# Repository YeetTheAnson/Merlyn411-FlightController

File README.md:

# Merlyn411 Flight Controller

> [!TIP]
> The Merlyn411 is outdated! Check out the [Merlyn435](https://github.com/YeetTheAnson/Merlyn435-Flight-Stack/) for a more powerful and modern flight controller + ESC.

## Introduction

This is my custom AIO (No ESC) flight controller! I started this project because commercial flight controllers get very expensive very quickly as you demand for more features like integrated radio receivers. I took on the challenge of designing my own betaflight compatible flight controller and it was difficult especially since the board has only 2 layers to save as much cost as possible and it's also my first time working with RF in circuits.

This flight controller is designed for a wide range of drones from 2" to as big as you want it to, and supports battery voltage from 2s to 8s although it is recommended to use a maximum of 6s. The 25.5mm pattern should be compatible with almost all frames on the market

It also features many quality of life features like an integrated ExpressLRS (ELRS) 2.4GHz receiver, an onboard OSD which inserts telemetry directly into the FPV video feed, 16MB flash memory for flight & blackbox logging and a buzzer for identifying error codes and to locate the drone.

While the primary focus of this projet is the flight controller hardware and firmware, I have also included a guide for the full 3 inch long range / freestyle drone build that this board was designed for

-----

## Hardware Specifications

  - **MCU:** STM32F411CEU6 (100MHz, 512KB Flash)
  - **IMU:** MPU6500 (SPI)
  - **OSD:** AT7456E (SPI)
  - **Blackbox:** Winbond W25Q128 16MB Flash (SPI)
  - **Receiver:** Integrated 2.4GHz ExpressLRS (ESP8285 & SX1281)
  - **Power Supply:** 5v and 3.3v rails up to 1A (3.3v rail is limited to 250mA)
  - **Mounting:** 25.5mm x 25.5mm square mounting pattern with M3 holes
  - **Peripherals** Includes pads for using external receivers, GPS, Magnetometer, analog camera and VTX

Note: The IMU should be in the forward facing direction if the USB C connector is facing forward and to the right. Adjust the mounting orientation accordingly in betaflight

-----

## Pinout
### External Headers

| Header | Pin Name | STM32 Pin | Description |
| :--- | :--- | :--- | :--- |
| **GPS** | `T` | PA9 | UART1 TX (Connect to GPS RX) |
| | `R` | PA10 | UART1 RX (Connect to GPS TX) |
| | `3` | - | 3.3V Power Out |
| | `5` | - | 5V Power out |
| | `G` | - | Ground |
| | `C` | PB8 | I2C1 SCL (For Magnetometer) |
| | `D` | PB9 | I2C1 SDA (For Magnetometer) |
| **VTX** | `B`| - | Video Bypass (Direct from camera) |
| | `O` | - | Analog Video Out (From AT7456E) |
| | `G` | - | Ground |
| | `B+` | - | Battery Output |
| **CAM** | `B` | - | Video Bypass (Direct to VTX) |
| | `I` | - | Analog Video Input (From camera) |
| | `G` | - | Ground |
| | `5` | - | 5V Power Out |
| **SWD** | `C` | PA14 | SWCLK (Debug & Flash) |
| | `D` | PA13 | SWDIO (Debug & Flash) |
| | `R` | NRST | NRST (Debug & Flash) |
| | `B` | BOOT0 | BOOT0 (Debug & Flash) |
| **ESC** | `1-4` | PB4-PB7 | Motor Signal Outputs |
| **BAT** | `BAT+` | - | Battery Positive Input |
| | `BAT-` | - | Battery Negative Input |
| **CAP** | `CAP+` | - | Capacitor Anode |
| | `CAP-` | - | Capacitor Cathode |
| **PWR** | `G` | - | Ground |
| | `3` | - | 3.3V Power Out |
| | `5` | - | 5V Power Out |
| **Test Points** | `X` | PA15 | SmartAudio (Softserial 1 TX) |
| | `S` | PA15 | Current Sense Pin (From ESC) |
| | `T` | PA2 | ESP8285 RX Pin (STM32 TX PIN) |
| | `R` | PA3 | ESP8285 TX Pin (STM32 RX PIN) |

### Test Points & Pads

  - **External RX:**. Use these if you disable the internal ELRS receiver to connect other modules. Pad is labelled T and R on silkscreen.
  - **IRC Tramp and SmartAudio:** Connect VTX IRC or SmartAudio pin to the pad labeled with X on the silkscreen
  - **Current Sense:** Connect to ESC current sense pin. Pad is labelled S on silkscreen
  - **ENA & FSH:** Bridge ENA jumper to disable internal ELRS receiver. Bridge FSH jumper to put internal ELRS to flashing mode.
  - **Boot Mode (STM32):** To enter DFU mode for the flight controller, short the SWD B pad to any +3.3v rail while plugging in the USB.

-----

## Flight Controller Firmware (Betaflight)

Because this is a custom hardware layout, I believe that there is no standard targets that has the exact pin mapping as my flight controller. You must compile the firmware with the custom target definition in [/firmware/MERLYN411](https://github.com/YeetTheAnson/Merlyn411-FlightController/tree/main/firmware/MERLYN411) or use the pre compiled firmware in [/firmware/COMPILED](https://github.com/YeetTheAnson/Merlyn411-FlightController/tree/main/firmware/COMPILED).

> [!TIP]
> You can use flash another target to the flight controller and use betaflight CLI to remap the pin resource, however this is not recommended as the chosen target might not be compiled with a feature that this flight controller supports.

### How to build the firmware

1. Clone the [betaflight repository](https://github.com/betaflight/betaflight) using any UNIX terminal (use MYSYS2 MINGW64 on windows) and enter the directory
2. Enter `make configs` (install any required GCC toolchain if required)
3. Create a directory in betaflight/src/config/configs named `MERLYN411` and paste [config.h](https://github.com/YeetTheAnson/Merlyn411-FlightController/tree/main/firmware/MERLYN411/config.h) in the new directory
4. Enter `make MERLYN411` and the `.hex` file should appear in `betaflight/obj`

### Flashing the Flight Controller

1. **Via USB (DFU Mode):** Short the SWD `B` pad to 3.3v on the FC and plug in the USB C cable. Open Betaflight Configurator, select your compiled local `.hex` file, and click Flash Firmware.
2. **Via SWD:** If the bootloader is corrupted, connect an ST Link programmer to the `D`, `C`, and `D` (`R` is optional) pads and flash via STM32CubeProgrammer.

-----

## ExpressLRS Flashing

The internal ESP8285 and SX1281 receiver is wired to the STM32 via a hardware UART. It uses the standard **BETAFPV 2.4GHz Lite RX** firmware target. You can obtain the firmware binaries from the ELRS [site](https://expresslrs.github.io/web-flasher/) or from this repository in [/firmware/COMPILED](https://github.com/YeetTheAnson/Merlyn411-FlightController/tree/main/firmware/COMPILED). There's two way to flash the receiver:

### Method 1: Betaflight Passthrough

Note that betaflight must be installed and configured before passthrough works
1. Connect the FC via USB
2. Open the ExpressLRS Configurator [web flasher](https://expresslrs.github.io/web-flasher/) or app
3. Select `Receiver`
4. Select the `BETAFPV 2.4GHz Lite RX` target and press next
5. [OPTIONAL] Enter your bind phrase
6. Select the Betaflight Passthrough flashing method, press next and follow the steps

### Method 2: Manual Flashing

If the ESP8285 is bricked or passthrough fails, you can flash it directly using an FTDI adapter or another ESP8285/ESP8286/ESP32 or even an arduino

**Wiring the FTDI:**
The UART pads on the board are named relative to the STM32's perspective. Because the STM32's `TX` is connected to the ESP8285's `RX`, you must wire your FTDI adapter **RX to RX** and **TX to TX**.

  * FTDI `TX` -\> FC Pad `T`
  * FTDI `RX` -\> FC Pad `R`
  * FTDI `GND` -\> FC Pad `G`
  * FTDI `5V` -\> FC Pad `5` (or power via USB)

You must disable the STM32 when flashing via the T and R pad
using an external FTDI as it will intefere with the UART lines. You can disable the STM32 by shorting the SWD `R` pad to ground. Remember to short the `ENA` pads on the bottom side to put the ESP8285 into flashing mode.

-----

## Drone Assembly

While this project is mainly focused on the Merlyn411 flight controller, I designed it along with a high efficiency 3 inch cruiser drone in mind. If you want to recreate the full build, below is the component breakdown and assembly steps

### Component List
- **Flight Controller:** Merlyn411
- **ESC:** JHEMCU EM40A
- **Motors:** Sparkhobby 1303.5 5500KV
- **Propellers:** Gemfan 3016 Tri-Blade
- **VTX:** JHEMCU 600mW VTX
- **Camera:** Analog FPV micro(19mm) camera
- **Frame:** Custom frame
- **Battery:** 2S-4S LiPo or 2S/3S 18650 Li Ion packs

### Why 3D Printing the Frame is Not Recommended
Currently, I am using a custom frame that I 3D printed for prototyping. I strongly advise against using a 3D printed frame for your final build. The Merlyn411 uses the MPU6500 IMU, which is sensitive to mechanical noise and vibrations. 3D printed frames will flex and resonate significantly more than carbon fiber frames. This flexing will send noise into the gyro and resulting in terrible flight performance. Also the 3D printed frame will likely not survive a moderate impact.

### Fasteners
Because this is a custom stack with a 25.5mm FC and a 20mm ESC, the stack up is very specific. You will need:
* 6x M3 20mm Female to Female Brass Standoffs (Frame separation)
* 12x M3 6mm Screws (Frame to standoffs)
* 4x M2 Nuts (Stack base)
* 4x M2 16mm Screws (Main stack skewers)
* 8x M2 10mm Screws (Top stack/VTX skewers)
* 16x M2 6mm Screws (Motors)
* 4x M2 6mm Screws (Camera/Props)

### FC Stack
The Merlyn411 uses a 25.5x25.5mm mounting pattern (which is meant for AIO boards). However, I needed a standalone ESC which comes in standard sizes like 20x20mm.

To make these fit together, you must use a 3D printed adapter plate in [/production/3dPrint/boardAdapter.stl](https://github.com/YeetTheAnson/Merlyn411-FlightController/blob/main/production/3dPrint/boardAdapter.stl). 

**Stack Assembly Layer 1:**
1.  Place 4x M2 Nuts into the designated recesses in the bottom frame plate.
2. Push rubber grommets into the flight controller
3. Push 4x M2 16mm screws through the adapter plate, through the rubber grommet, and through the bottom plate into the M2 nuts

**Stack Assembly Layer 2:**
1. Push rubber grommets into the ESC
2. Push 4x M2 10mm screws through rubber grommets and through the adapter plate until it reaches another set of M2 nuts

### Mounting the VTX
The JHEMCU 600mW VTX mounts to the rear of the frame.
1.  Place 4x M2 Nuts into the bottom frame plate at in the rear
2. Push rubber grommets into the VTX
3.  Thread 4x M2 10mm screws through rubber grommets, down through the bottom plate, and into the nuts

### Final Assembly
1.  **Motors:** Mount the four 1303.5 5500KV motors to the arms using 16x M2 6mm screws (4 per motor). Ensure the screws do not touch the motor windings inside the bell.
2.  **Propellers:** Mount the Gemfan 3016 propeller. Pay attention to motor rotation directions (depending on your betaflight configuration, it could either be prop in or prop out). Fasten each prop with 2x M2 6mm screws.
3.  **Camera:** Mount the analog FPV camera to the front using 2x M2 6mm screws.
4.  **Closing the Frame:** Use the 6x M3 20mm standoffs and 12x M3 6mm screws to secure the top plate to the bottom plate

## Bill of Material
Note: The prices in USD are converted as of 31 March 2026 and prices may fluctuate. The requested funding is $200 as a buffer for the unstable prices. Any unused funds is returned.

| Item Name | Link | Vendor | Quantity | Total Price (USD) |
|----------|------|--------|----------|-------------------|
| 2450FM07D0034 | [Link](https://www.aliexpress.com/item/1005007939000699.html) | AliExpress | 1 | 6.40 |
| AliExpress Shipping |  | AliExpress | 1 | 3.15 |
| PCB |  | JLCPCB | 1 | 2.00 |
| PCB Assembly |  | JLCPCB | 1 | 79.49 |
| JLCPCB Shipping |  | JLCPCB | 1 | 6.02 |
| Sparkhobby 1303.5 5500KV motor | [Link](https://click.world.taobao.com/_b.QbWPiG) | Taobao | 4 | 22.50 |
| JHEMCU EM40A ESC | [Link](https://click.world.taobao.com/_b.ubW0U5) | Taobao | 1 | 18.11 |
| 19mm FPV Camera | [Link](https://click.world.taobao.com/_b.LbWPiH) | Taobao | 1 | 5.16 |
| JHEMCU 600mW VTX | [Link](https://click.world.taobao.com/_b.vbWPq7) | Taobao | 1 | 14.58 |
| M10 GPS & Magnetometer | [Link](https://click.world.taobao.com/_b.TbWPjE) | Taobao | 1 | 7.55 |
| Rubber Grommet Shock Mount | [Link](https://click.world.taobao.com/_b.XbWPTq) | Taobao | 12 | 0.80 |
| Gemfan 3016 | [Link](https://click.world.taobao.com/_b.4bW0jv) | Taobao | 1 | 1.75 |
| ELRS Dipole Antenna | [Link](https://click.world.taobao.com/_b.obW0UN) | Taobao | 1 | 0.90 |
| Taobao Tax |  | Taobao | 1 | 8.35 |
| Taobao Shipping |  | Taobao | 1 | 2.48 |
| 10k Resistor | [Link](https://shopee.com.my/100PCS-0603-1-SMD-Resistor-1.1K-~-100K-2K-10K-15K-20K-30K-51K-62K-75K-100K-Patch-resistance-i.1135937572.18786797162) | Shopee | 1 | 0.45 |
| 100nF Capacior | [Link](https://shopee.com.my/100PCS-0603-SMD-Chip-Multilayer-Ceramic-Capacitor-330PF-22uF-1nF-10nF-15nF-100nF-0.1uF-1uF-2.2uF-4.7uF-10uF-i.1135937572.21395687476) | Shopee | 1 | 0.45 |
| 22uF Tantalum | [Link](https://shopee.com.my/10PCS-A-Type-Tantalum-Capacitor-100uf-150uf-220uf-330uf-470uf-680uf-6V-6.3V-10V-16V-25V-35V-50V-4.7-6.8-10-15-22-33-47uf-i.1135937572.21795687477) | Shopee | 1 | 0.88 |
| USBCL6-2SC6 | [Link](https://shopee.com.my/50Pcs-5pcs-USBLC-USBLC6-2SC6-SOT-23-6-USBLC6-SOT-UL26-SOT23-Low-Capacitor-Capacitance-2-wire-ESD-Static-Protection-Chip-IC-i.1649836180.41923888381) | Shopee | 1 | 0.83 |
| 2N7002LT | [Link](https://shopee.com.my/2N7002LT-2N7002-7002-N-Channel-MOSFET-N-CH-SOT23-SMD-IC-MOS-FET-Field-Effect-Tube-SOT-23-i.1649836180.44952514481) | Shopee | 1 | 0.79 |
| 9650 Active Buzzer | [Link](https://shopee.com.my/SMD-Buzzer-9018-9025-9045-1109-9650-3V-5V-Magnetic-Mini-Active-Passive-Piezo-Buzzers-Loudspeaker-Loud-Beep-Alarm-For-Arduino-i.1649836180.46152504777) | Shopee | 1 | 1.05 |
| SPX3819 | [Link](https://shopee.com.my/10pcs-5pcs-SPX3819-SPX3819M5-L-3-3-TR-SOT-23-5-SPX3819M5-3.3-SPX3819M5-3-3-TR-SOT23-3.3V-500mA-Regulator-LDO-IC-New-Original-i.1649836180.50452276303) | Shopee | 1 | 1.45 |
| 8040 68uH Inductor | [Link](https://shopee.com.my/10pcs-4030-SWPA4030S-4020-5040-6045-8040-SMD-Power-Inductor-2.2uH-3.3uH-4.7uH-6.8uH-10uH-15uH-22uH-33uH-47uH-56uH-Wire-Wound-i.1649836180.55202484435) | Shopee | 1 | 1.51 |
| SPX Express Shipping |  | Shopee | 2 | 2.56 |
| **GRAND TOTAL** |  |  |  | **189.21** |

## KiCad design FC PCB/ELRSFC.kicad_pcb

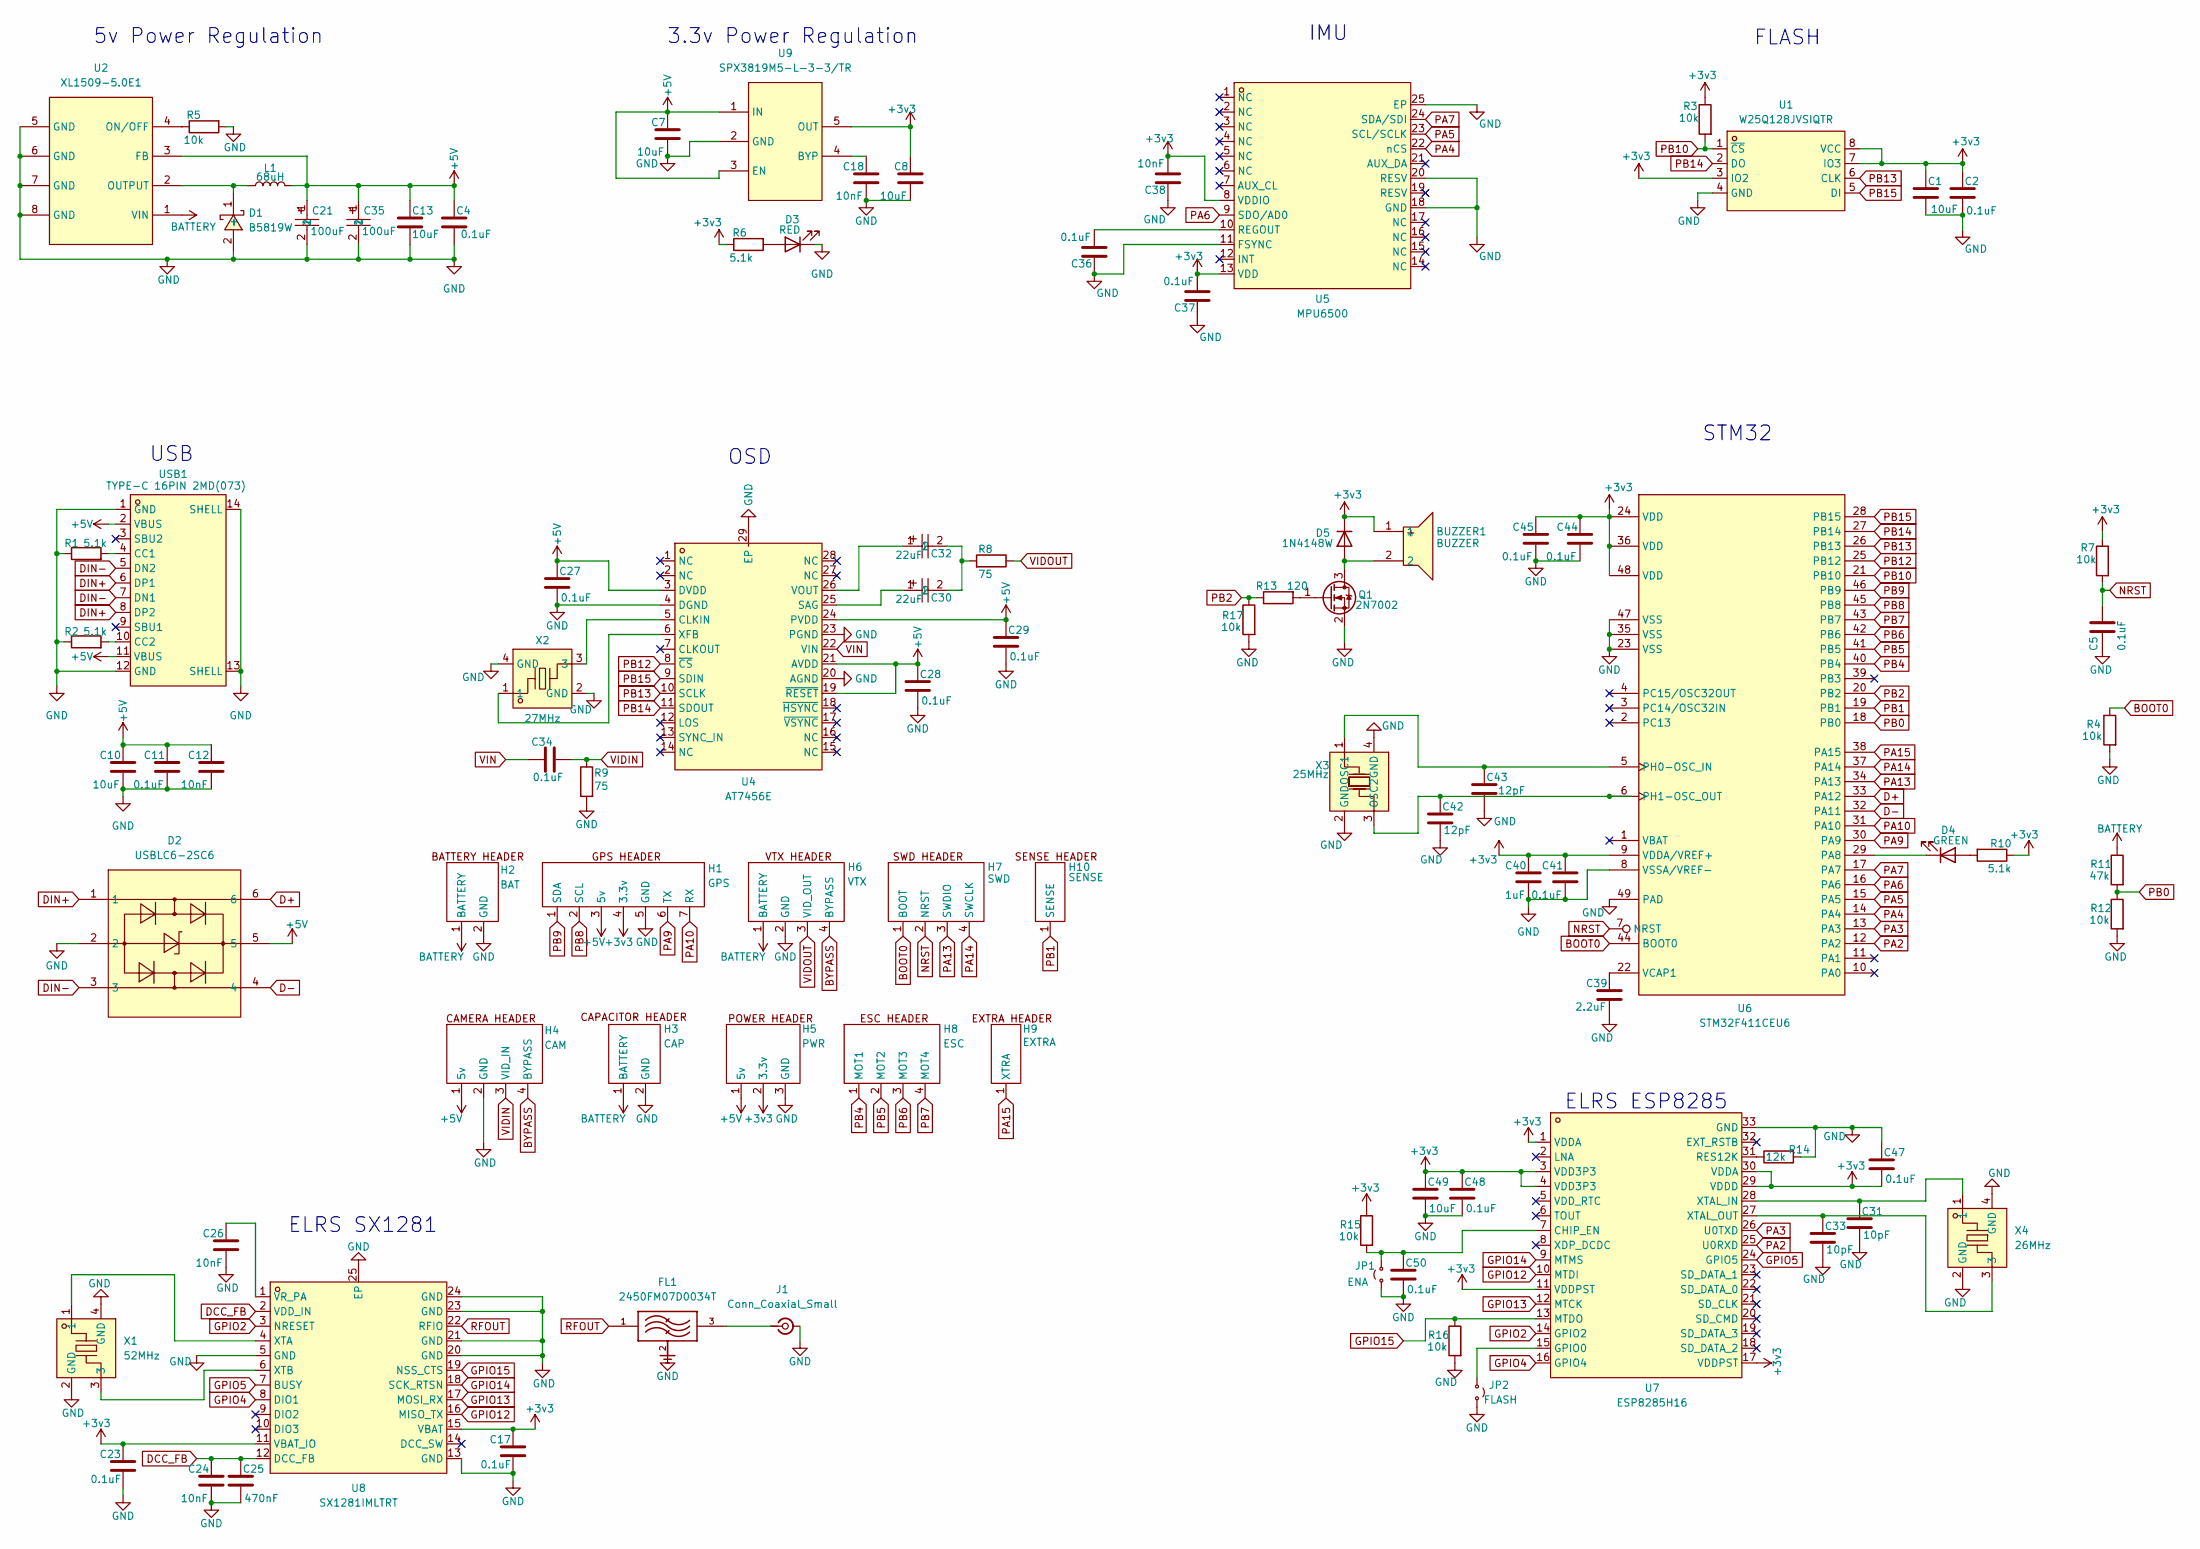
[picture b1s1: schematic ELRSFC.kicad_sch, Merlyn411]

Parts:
BUZZER1: BUZZER; BUZ-SMD_L9.6-W9.6-LS10.0-R; LCSC Part C96127
C1, C7, C8, C10, C13, C49: 10uF; C_0402_1005Metric; LCSC Part C15525
C2, C4, C11, C17, C23, C27, C28, C29, C34, C36, C37, C41, C44, C45, C47, C48, C50: 0.1uF; C_0402_1005Metric; LCSC Part C307331
C5: 0.1uF; C_0603_1608Metric
C12, C18, C24, C26, C38: 10nF; C_0402_1005Metric; LCSC Part C15195
C21, C35: 100uF; CASE-B_3528; LCSC Part C16133
C25: 470nF; C_0603_1608Metric; LCSC Part C1623
C30, C32: 22uF; CAP-SMD_L3.2-W1.6-RD-C7171
C31, C33: 10pF; C_0402_1005Metric; LCSC Part C32949
C39: 2.2uF; C_0402_1005Metric; LCSC Part C12530
C40: 1uF; C_0402_1005Metric; LCSC Part C52923
C42, C43: 12pF; C_0402_1005Metric; LCSC Part C1547
D1: B5819W; SOD-123_L2.7-W1.6-LS3.7-RD-1; LCSC Part C8598
D2: USBLC6-2SC6; SOT-23-6_L2.9-W1.6-P0.95-LS2.8-BL; LCSC Part C7519
D3: RED; LED_0805_2012Metric; LCSC Part C84256
D4: GREEN; LED_0805_2012Metric; LCSC Part C2297
D5: 1N4148W; D_SOD-123
FL1: 2450FM07D0034T; FIL_2450FM07D0034T; PARTREV 1.2
H1: GPS
H2: BAT
H3: CAP
H4: CAM
H5: PWR
H6: VTX
H7: SWD
H8: ESC
H9: EXTRA
H10: SENSE
J1: Conn_Coaxial_Small; UFL
JP1: ENA
JP2: FLASH
L1: 68uH; L_Sunlord_SWPA8040S
Q1: 2N7002; SOT-23
R1, R2, R6, R10: 5.1k; R_0402_1005Metric; LCSC Part C25905
R3, R5, R12, R15, R16, R17: 10k; R_0402_1005Metric; LCSC Part C25744
R4, R7: 10k; R_0603_1608Metric
R8, R9: 75; R_0603_1608Metric; LCSC Part C4275
R11: 47k; R_0402_1005Metric; LCSC Part C25792
R13: 120; R_0402_1005Metric; LCSC Part C25079
R14: 12k; R_0402_1005Metric; LCSC Part C25752
U1: W25Q128JVSIQTR; SOIC-8_L5.3-W5.3-P1.27-LS8.0-BL; LCSC Part C97521
U2: XL1509-5.0E1; SOIC-8_L5.0-W4.0-P1.27-LS6.0-BL; LCSC Part C61063
U4: AT7456E; TSSOP-28_L9.7-W4.4-P0.65-LS6.4-BL-EP-2; LCSC Part C82351
U5: MPU6500; QFN-24_L3.0-W3.0-P0.40-BL-EP; LCSC Part C50278
U6: STM32F411CEU6; UFQFPN-48_L7.0-W7.0-P0.50-BL-EP; LCSC Part C60420
U7: ESP8285H16; QFN-32_L5.0-W5.0-P0.50-TL-EP3.7; LCSC Part C967019
U8: SX1281IMLTRT; QFN-24_L4.0-W4.0-P0.50-TL-EP2.6; LCSC Part C2151551
U9: SPX3819M5-L-3-3/TR; SOT-23-5_L3.0-W1.7-P0.95-LS2.8-BL; LCSC Part C9055
USB1: TYPE-C 16PIN 2MD(073); USB-C-SMD_TYPE-C-6PIN-2MD-073; LCSC Part C2765186
X1: 52MHz; CRYSTAL-SMD_4P-L2.0-W1.6-BL; LCSC Part C3034316
X2: 27MHz; CRYSTAL-SMD_4P-L2.0-W1.6-BL; LCSC Part C648952
X3: 25MHz; CRYSTAL-SMD_4P-L3.2-W2.5-BL; LCSC Part C9006
X4: 26MHz; CRYSTAL-SMD_4P-L2.0-W1.6-BL; LCSC Part C19272774

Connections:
+3v3: BUZZER1.1, C1.1, C2.1, C8.1, C17.1, C23.1, C37.2, C38.2, C40.1, C41.1, C44.1, C45.1, C47.2, C48.1, C49.1, D5.1 (K), H1.4 (3.3v), H5.2 (3.3v), R3.1, R6.1, R7.1, R10.1, R15.1, U1.3 (IO2), U1.7 (IO3), U1.8 (VCC), U5.8 (VDDIO), U5.13 (VDD), U6.9 (VDDA/VREF+), U6.24 (VDD), U6.36 (VDD), U6.48 (VDD), U7.1 (VDDA), U7.3 (VDD3P3), U7.4 (VDD3P3), U7.11 (VDDPST), U7.17 (VDDPST), U7.29 (VDDD), U7.30 (VDDA), U8.11 (VBAT_IO), U8.15 (VBAT), U9.5 (OUT)
+5V: C4.1, C7.1, C10.1, C11.1, C12.1, C13.1, C21.1, C27.1, C28.1, C29.1, C35.1, D2.5, H1.3 (5v), H4.1 (5v), H5.1 (5v), L1.2, U2.3 (FB), U4.3 (DVDD), U4.19 (~RESET), U4.21 (AVDD), U4.24 (PVDD), U9.1 (IN), U9.3 (EN), USB1.2 (VBUS), USB1.11 (VBUS)
BATTERY: H2.1 (BATTERY), H3.1 (BATTERY), H6.1 (BATTERY), R11.1, U2.1 (VIN)
BOOT0: H7.1 (BOOT), R4.1, U6.44 (BOOT0)
BYPASS: H4.4 (BYPASS), H6.4 (BYPASS)
D+: D2.6, U6.33 (PA12)
D-: D2.4, U6.32 (PA11)
DCC_FB: C24.1, C25.1, U8.2 (VDD_IN), U8.12 (DCC_FB)
DIN+: D2.1, USB1.6 (DP1), USB1.8 (DP2)
DIN-: D2.3, USB1.5 (DN2), USB1.7 (DN1)
GND: C1.2, C2.2, C4.2, C5.1, C7.2, C8.2, C10.2, C11.2, C12.2, C13.2, C17.2, C18.2, C21.2, C23.2, C24.2, C25.2, C26.2, C27.2, C28.2, C29.2, C31.2, C33.2, C35.2, C36.1, C37.1, C38.1, C39.2, C40.2, C41.2, C42.2, C43.2, C44.2, C45.2, C47.1, C48.2, C49.2, C50.2, D1.2 (+), D2.2, D3.1 (K), FL1.2, FL1.4, H1.5 (GND), H2.2 (GND), H3.2 (GND), H4.2 (GND), H5.3 (GND), H6.2 (GND), J1.2 (Ext), JP1.1 (A), JP2.1 (A), Q1.2 (S), R1.1, R2.1, R4.2, R5.2, R9.2, R12.2, R14.2, R16.2, R17.2, U1.4 (GND), U2.5 (GND), U2.6 (GND), U2.7 (GND), U2.8 (GND), U4.4 (DGND), U4.20 (AGND), U4.23 (PGND), U4.29 (EP), U5.11 (FSYNC), U5.18 (GND), U5.20 (RESV), U5.25 (EP), U6.8 (VSSA/VREF-), U6.23 (VSS), U6.35 (VSS), U6.47 (VSS), U6.49 (PAD), U7.33 (GND), U8.5 (GND), U8.13 (GND), U8.20 (GND), U8.21 (GND), U8.23 (GND), U8.24 (GND), U8.25 (EP), U9.2 (GND), USB1.1 (GND), USB1.12 (GND), USB1.13 (SHELL), USB1.14 (SHELL), X1.2 (GND), X1.4 (GND), X2.2 (GND), X2.4 (GND), X3.2 (GND), X3.4 (GND), X4.2 (GND), X4.4 (GND)
GPIO2: U7.14 (GPIO2), U8.3 (NRESET)
GPIO4: U7.16 (GPIO4), U8.8 (DIO1)
GPIO5: U7.24 (GPIO5), U8.7 (BUSY)
GPIO12: U7.10 (MTDI), U8.16 (MISO_TX)
GPIO13: U7.12 (MTCK), U8.17 (MOSI_RX)
GPIO14: U7.9 (MTMS), U8.18 (SCK_RTSN)
GPIO15: R16.1, U7.13 (MTDO), U8.19 (NSS_CTS)
NRST: C5.2, H7.2 (NRST), R7.2, U6.7 (NRST)
unnamed: C30.2, C32.2, R8.2
unnamed: D1.1 (-), L1.1, U2.2 (OUTPUT)
unnamed: D3.2 (A), R6.2
unnamed: D4.2 (A), R10.2
unnamed: D4.1 (K), U6.29 (PA8)
unnamed: BUZZER1.2, D5.2 (A), Q1.3 (D)
unnamed: FL1.3, J1.1 (In)
unnamed: C50.1, JP1.2 (B), R15.2, U7.7 (CHIP_EN)
unnamed: JP2.2 (B), U7.15 (GPIO0)
unnamed: Q1.1 (G), R13.2
unnamed: R5.1, U2.4 (ON/OFF)
unnamed: U4.5 (CLKIN), X2.3
unnamed: C30.1, U4.25 (SAG)
unnamed: C32.1, U4.26 (VOUT)
unnamed: U4.6 (XFB), X2.1
unnamed: C36.2, U5.10 (REGOUT)
unnamed: C43.1, U6.5 (PH0-OSC_IN), X3.1 (OSC1)
unnamed: C42.1, U6.6 (PH1-OSC_OUT), X3.3 (OSC2)
unnamed: C39.1, U6.22 (VCAP1)
unnamed: R14.1, U7.31 (RES12K)
unnamed: C31.1, U7.28 (XTAL_IN), X4.1
unnamed: C33.1, U7.27 (XTAL_OUT), X4.3
unnamed: C26.1, U8.1 (VR_PA)
unnamed: U8.4 (XTA), X1.1
unnamed: U8.6 (XTB), X1.3
unnamed: C18.1, U9.4 (BYP)
unnamed: R1.2, USB1.4 (CC1)
unnamed: R2.2, USB1.10 (CC2)
PA2: U6.12 (PA2), U7.25 (U0RXD)
PA3: U6.13 (PA3), U7.26 (U0TXD)
PA4: U5.22 (nCS), U6.14 (PA4)
PA5: U5.23 (SCL/SCLK), U6.15 (PA5)
PA6: U5.9 (SDO/AD0), U6.16 (PA6)
PA7: U5.24 (SDA/SDI), U6.17 (PA7)
PA9: H1.6 (TX), U6.30 (PA9)
PA10: H1.7 (RX), U6.31 (PA10)
PA13: H7.3 (SWDIO), U6.34 (PA13)
PA14: H7.4 (SWCLK), U6.37 (PA14)
PA15: H9.1 (XTRA), U6.38 (PA15)
PB0: R11.2, R12.1, U6.18 (PB0)
PB1: H10.1 (SENSE), U6.19 (PB1)
PB2: R13.1, R17.1, U6.20 (PB2)
PB4: H8.1 (MOT1), U6.40 (PB4)
PB5: H8.2 (MOT2), U6.41 (PB5)
PB6: H8.3 (MOT3), U6.42 (PB6)
PB7: H8.4 (MOT4), U6.43 (PB7)
PB8: H1.2 (SCL), U6.45 (PB8)
PB9: H1.1 (SDA), U6.46 (PB9)
PB10: R3.2, U1.1 (~CS), U6.21 (PB10)
PB12: U4.8 (~CS), U6.25 (PB12)
PB13: U1.6 (CLK), U4.10 (SCLK), U6.26 (PB13)
PB14: U1.2 (DO), U4.11 (SDOUT), U6.27 (PB14)
PB15: U1.5 (DI), U4.9 (SDIN), U6.28 (PB15)
RFOUT: FL1.1, U8.22 (RFIO)
VIDIN: C34.1, H4.3 (VID_IN), R9.1
VIDOUT: H6.3 (VID_OUT), R8.1
VIN: C34.2, U4.22 (VIN)

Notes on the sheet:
ELRS ESP8285
STM32
3.3v Power Regulation
FLASH
OSD
IMU
USB
5v Power Regulation
ELRS SX1281

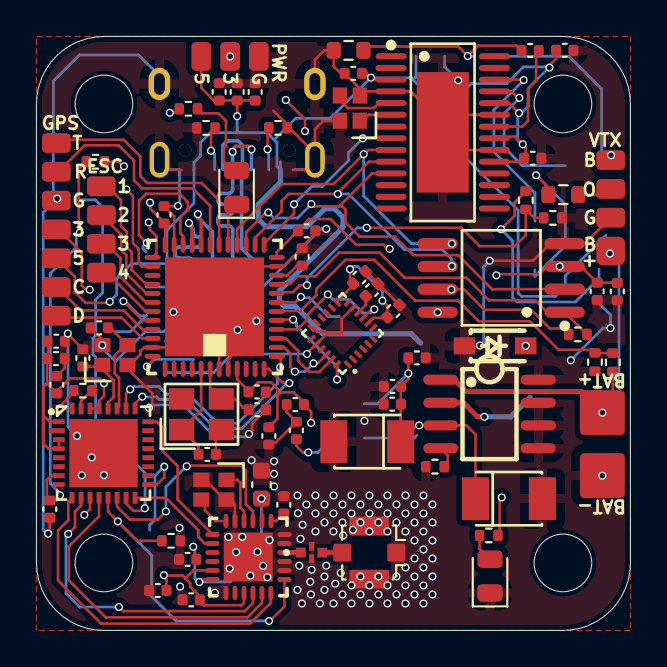
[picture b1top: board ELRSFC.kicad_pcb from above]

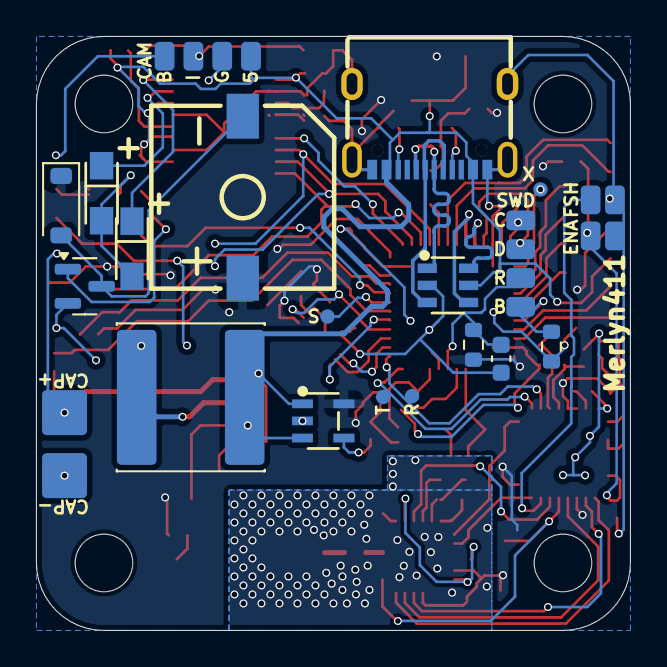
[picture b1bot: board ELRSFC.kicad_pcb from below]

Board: 2 copper layers, 33.0 x 33.0 mm, 92 parts (19 on the bottom side), 76 nets.

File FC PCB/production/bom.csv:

Designator,Footprint,Quantity,Value,LCSC Part #
BUZZER1,BUZ-SMD_L9.6-W9.6-LS10.0-R,1,BUZZER,C96127
"C1, C10, C13, C49, C7, C8",0402,6,10uF,C15525
"C11, C17, C2, C23, C27, C28, C29, C34, C36, C37, C4, C41, C44, C45, C47, C48, C50",0402,17,0.1uF,C307331
"C12, C18, C24, C26, C38",0402,5,10nF,C15195
"C21, C35",CASE-B_3528,2,100uF,C16133
C25,0603,1,470nF,C1623
"C30, C32",CAP-SMD_L3.2-W1.6-RD-C7171,2,22uF,
"C31, C33",0402,2,10pF,C32949
C39,0402,1,2.2uF,C12530
C40,0402,1,1uF,C52923
"C42, C43",0402,2,12pF,C1547
C5,0603,1,0.1uF,
D1,SOD-123_L2.7-W1.6-LS3.7-RD-1,1,B5819W,C8598
D2,SOT-23-6_L2.9-W1.6-P0.95-LS2.8-BL,1,USBLC6-2SC6,C7519
D3,0805,1,RED,C84256
D4,0805,1,GREEN,C2297
FL1,FIL_2450FM07D0034T,1,2450FM07D0034T,
H1,GPS,1,GPS,
H2,BAT,1,BAT,
H3,CAP,1,CAP,
H4,CAM,1,CAM,
H5,PWR,1,PWR,
H6,VTX,1,VTX,
H7,SWD,1,SWD,
H8,ESC,1,ESC,
J1,UFL,1,Conn_Coaxial_Small,
JP1,ENA,1,ENA,
JP2,FLASH,1,FLASH,
L1,L_Sunlord_SWPA8040S,1,68uH,
"R1, R10, R2, R6",0402,4,5.1k,C25905
R11,0402,1,47k,C25792
"R12, R15, R16, R3, R5",0402,5,10k,C25744
R13,0402,1,120,C25079
R14,0402,1,12k,C25752
"R4, R7",0603,2,10k,
"R8, R9",0603,2,75,C4275
U1,SOIC-8_L5.3-W5.3-P1.27-LS8.0-BL,1,W25Q128JVSIQTR,C97521
U2,SOIC-8_L5.0-W4.0-P1.27-LS6.0-BL,1,XL1509-5.0E1,C61063
U4,TSSOP-28_L9.7-W4.4-P0.65-LS6.4-BL-EP-2,1,AT7456E,C82351
U5,QFN-24_L3.0-W3.0-P0.40-BL-EP,1,MPU6500,C50278
U6,UFQFPN-48_L7.0-W7.0-P0.50-BL-EP,1,STM32F411CEU6,C60420
U7,QFN-32_L5.0-W5.0-P0.50-TL-EP3.7,1,ESP8285H16,C967019
U8,QFN-24_L4.0-W4.0-P0.50-TL-EP2.6,1,SX1281IMLTRT,C2151551
U9,SOT-23-5_L3.0-W1.7-P0.95-LS2.8-BL,1,SPX3819M5-L-3-3/TR,C9055
USB1,USB-C-SMD_TYPE-C-6PIN-2MD-073,1,TYPE-C 16PIN 2MD(073),C2765186
X1,CRYSTAL-SMD_4P-L2.0-W1.6-BL,1,52MHz,C3034316
X2,CRYSTAL-SMD_4P-L2.0-W1.6-BL,1,27MHz,C648952
X3,CRYSTAL-SMD_4P-L3.2-W2.5-BL,1,25MHz,C9006
X4,CRYSTAL-SMD_4P-L2.0-W1.6-BL,1,26MHz,C19272774

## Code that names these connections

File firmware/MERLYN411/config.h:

/*
 * This file is part of Betaflight.
 *
 * Betaflight is free software. You can redistribute this software
 * and/or modify this software under the terms of the GNU General
 * Public License as published by the Free Software Foundation,
 * either version 3 of the License, or (at your option) any later
 * version.
 *
 * Betaflight is distributed in the hope that it will be useful,
 * but WITHOUT ANY WARRANTY; without even the implied warranty of
 * MERCHANTABILITY or FITNESS FOR A PARTICULAR PURPOSE.
 *
 * See the GNU General Public License for more details.
 *
 * You should have received a copy of the GNU General Public
 * License along with this software.
 *
 * If not, see <http://www.gnu.org/licenses/>.
 */

#pragma once

#define FC_TARGET_MCU      STM32F411

#define BOARD_NAME         MERLYN411
#define MANUFACTURER_ID    ANSON

// ---- INTERNAL COMPONENTS ----
#define USE_ACC
#define USE_ACC_MPU6500
#define USE_ACC_SPI_MPU6500

#define USE_GYRO
#define USE_GYRO_MPU6500
#define USE_GYRO_SPI_MPU6500

#define USE_MAX7456

#define USE_FLASH
#define USE_FLASH_W25Q128FV

// ---- EXTERNAL CONNECTABLE COMPONENTS ---
#define USE_MAG
#define USE_MAG_AK8963
#define USE_MAG_AK8975
#define USE_MAG_HMC5883
#define USE_MAG_IST8310
#define USE_MAG_LIS2MDL
#define USE_MAG_LIS3MDL
#define USE_MAG_QMC5883
#define USE_MPU9250_MAG
#define USE_MAG_MPU925X_AK8963

#define USE_GPS
#define USE_RANGEFINDER
#define USE_ALTITUDE_HOLD
#define USE_POSITION_HOLD

#define USE_TELEMETRY
#define USE_TELEMETRY_LTM
#define USE_TELEMETRY_CRSF
#define USE_TELEMETRY_GHST
#define USE_TELEMETRY_HOTT
#define USE_TELEMETRY_IBUS
#define USE_TELEMETRY_SRXL
#define USE_TELEMETRY_MAVLINK
#define USE_TELEMETRY_SMARTPORT
#define USE_TELEMETRY_FRSKY_HUB
#define USE_TELEMETRY_IBUS_EXTENDED

// ---- PIN MAPPING ----
#define LED0_PIN             PA8

#define ADC_VBAT_PIN         PB0
#define ADC_CURR_PIN         PB1
#define BEEPER_PIN           PB2
#define BEEPER_INVERTED

#define MOTOR1_PIN           PB4
#define MOTOR2_PIN           PB5
#define MOTOR3_PIN           PB6
#define MOTOR4_PIN           PB7

#define UART1_TX_PIN         PA9
#define UART1_RX_PIN         PA10
#define UART2_TX_PIN         PA2
#define UART2_RX_PIN         PA3

#define USE_SOFTSERIAL
#define USE_SOFTSERIAL1
#define SOFTSERIAL1_TX_PIN   PA15

#define I2C1_SCL_PIN         PB8
#define I2C1_SDA_PIN         PB9

#define SPI1_SCK_PIN         PA5
#define SPI1_SDI_PIN         PA6
#define SPI1_SDO_PIN         PA7

#define SPI2_SCK_PIN         PB13
#define SPI2_SDI_PIN         PB14
#define SPI2_SDO_PIN         PB15

#define GYRO_1_CS_PIN        PA4
#define FLASH_CS_PIN         PB10
#define MAX7456_SPI_CS_PIN   PB12

// ---- TIMER MAPPING ----
#define TIMER_PIN_MAPPING \
    TIMER_PIN_MAP( 1, PB4 , 1,  0) \
    TIMER_PIN_MAP( 2, PB5 , 1,  0) \
    TIMER_PIN_MAP( 3, PB6 , 1,  0) \
    TIMER_PIN_MAP( 4, PB7 , 1,  0) \
    TIMER_PIN_MAP( 5, PA15, 1,  0)

// ---- HARDWARE INSTANCES ----
#define ADC1_DMA_OPT         1
#define MAG_I2C_INSTANCE     (I2CDEV_1)
#define BARO_I2C_INSTANCE    (I2CDEV_1)
#define GYRO_1_SPI_INSTANCE  SPI1
#define FLASH_SPI_INSTANCE   SPI2
#define MAX7456_SPI_INSTANCE SPI2
#define SYSTEM_HSE_MHZ       25

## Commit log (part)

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2026-03-21 Third journal entry
2026-03-22 Fourth journal entry
2026-03-22 Fifth journal entry
2026-03-23 Sixth entry
2026-03-23 Seventh entry
2026-03-24 Eight entry
2026-03-25 Ninth entry
2026-03-27 high cortisol
2026-03-29 (hopefully) finalized PCB
2026-03-31 Almost finalized
2026-03-31 Update links in README for consistency
2026-03-31 checkpoint
2026-03-31 Rename droneRender1.PNG to droneRender1.png
2026-03-31 final. Hopefully. The last commit required to fix anything
2026-03-31 whoops added warning about imu orientation
2026-04-01 Added 0.15mm board size on each edge for v cut clearance
2026-04-01 fixed readme typo
2026-04-09 Updated screw and nut hole dimensions
2026-04-14 Updated frame to fit VTX antenna, cutout for GPS, fix readme typo
2026-04-16 Enabled softserial, updated to betaflight 2025.12.2, uploaded recommended config
2026-04-16 Enabled softserial, uploaded recommended config
2026-04-16 FIX Enabled softserial, updated to betaflight 2025.12.2, uploaded recommended config
2026-04-16 FIX config
2026-04-21 Fixed buzzer configuration, updated firmware config.h and hex for fixes, updated ideal settings file, uploaded gps config file, updated 3d models
2026-05-28 Updated GPS and betaflight config, reinforced drone frame and made it work for 2.5" instead of 3" props
